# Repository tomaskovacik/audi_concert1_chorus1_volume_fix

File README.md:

> ## ⚠️ v2.0.0 — Important notice
>
> **Firmware v2.0.0 is only suitable for HWv5 boards.** It will NOT work correctly on older hardware revisions (v1–v4).
>
> This release is currently **under real-life / daily-use testing**. If you experience issues, please open a [GitHub issue](https://github.com/tomaskovacik/audi_concert1_chorus1_volume_fix/issues).
>
> ### What changed in v2.0.0 (not in release notes — no PRs were used)
>
> - **Switched to official STMicroelectronics STM32 Arduino core** (replaces Roger Clark's libmaple/stm32duino community core)
> - **Hardware SPI** used for front-panel communication (via STM32 core SPI peripheral)
> - **FlexWire** software I2C library used for TDA7342 volume chip communication on PB10/PB11  
>   (STM32F103C6 has only one I2C peripheral; hardware I2C2 does not exist on this chip)
> - **Persistent config** saved to last flash page (volume level, GALA, TA) — replaces EEPROM emulation from older cores
> - **GALA** (speed-dependent volume) support via VSS pulse timing on PB5
> - **CI** updated to build and release firmware binary automatically on git tags

Software and hardware to fix volume problem on audi concert1/chorus1 units made by blaupunkt. More about this problem in [this](https://github.com/tomaskovacik/audi_concert1_chorus1_volume_fix/wiki/Problem-of-Some-AUDI-Chorus-and-AUDI-Concert-Autoradio-Models,-or-%22Delayed-Action-Mine%22-from-Blaupunkt-Company) wiki page which is copy from [here](https://web.archive.org/web/20071017195907/http://erta.ru/review/chorus-problem_eng.shtml).

#### Compatible radios:

These are 100% compatible, manufactured by Blaupunkt:
```
Audi Chorus - 7 646 243 380 (4B0 035 152)
Audi Chorus A8 - 7 647 243 380
Audi Concert - 7 646 248 380 (4B0 035 186)
Audi Concert A8 - 7 647 248 380 (4D0 035 186A)
Audi Concert Navi - 7 647 249 380 (4B0 035 186B)
AUDI	CONCERT TT AUZ1Z3	7 648 244 380 (4B0 035 186D)
```
Maybe for these, drop me a message with pictures of radio from outside and inside, and I can check if your radio is compatible with this module:
```
AUDI	CHORUS A3	7 640 251 380
AUDI	CHORUS A8	7 648 243 380
AUDI	CHORUS AUZ1Z2	7 647 245 380   4B0 035 152A
AUDI	CHORUS M4 AUZ1Z2	7 648 245 380   4B0 035 152B
AUDI	CHORUS M4 AUZ1Z2	7 648 245 380   4B0 035 152B
AUDI	CONCERT A8	7 648 248 380
AUDI	CONCERT M4 AUZ1Z3	7 648 247 380   4B0 035 186C
```
#### Not compatible radios

Audio Concert made by Panasonic/Matsushita (8L0 035 186A, possible other codes ).This radio from this manufacturer did not have problems with volume (if it has, the problem is in volume rotary encoder)

There are other radios manufactured by Blaupunkt called Audi Concert Plus, which are not compatible:
```
AUDI	CONCERT PLUS AUZ1Z3	7 649 246 380   4B0 035 186E
AUDI	CONCERT PLUS A8 AUZ1Z3	7 649 249 380   4D0 035 186F
```
These use a different design and so are not compatible with this module. I never read that these radios did have a volume problem. If there is one then it is most likely a problem with volume rotary encoder.

#### Issues
Known issues <a href="https://github.com/tomaskovacik/audi_concert1_chorus1_volume_fix/issues">are here</a>

#### Video
Module in action: 

#### Schematics:

Schematics in <a href="https://github.com/tomaskovacik/audi_concert1_chorus1_volume_fix/blob/master/HW/audi_concert1_chorus1_volume_fix/audi_concert1_chorus1_volume_fix.pdf">pdf</a>.

Assemble plan for latest v5 is <a href="https://tomaskovacik.github.io/audi_concert1_chorus1_volume_fix/HW/audi_concert1_chorus1_volume_fix/bom_v5/ibom.html">here</a>. Components with value prefi NP_ are not required (not populated). These are there for future features. 1k_GALA resistor has to be populated if SW with <a href="https://github.com/tomaskovacik/audi_concert1_chorus1_volume_fix/blob/gala/SW/audi_volume_fix_stm32/audi_volume_fix_stm32.ino">gala</a> support is used (SW from gala branch). AP for old v1 hw is <a href="https://raw.githubusercontent.com/tomaskovacik/audi_concert1_chorus1_volume_fix/master/HW/audi_concert1_chorus1_volume_fix/assemble_plan1_0.png">here</a>.

Pictures of finished product:

Bottom side, with PLCC52 socket, inside part of pastic need to be cut:

Upper side, with comments to sockets

How to wire it (currently without intefacing with front pannel)

# COPYING

Everything is under GPLv3

# CONTRIBUTION

Contributions are welcome

# PCBs

PCBs are on sale also as whole product, kitt (PCB, soldered crystals, unsoldered preprogramed IC, pasives,PLCC52 socket)

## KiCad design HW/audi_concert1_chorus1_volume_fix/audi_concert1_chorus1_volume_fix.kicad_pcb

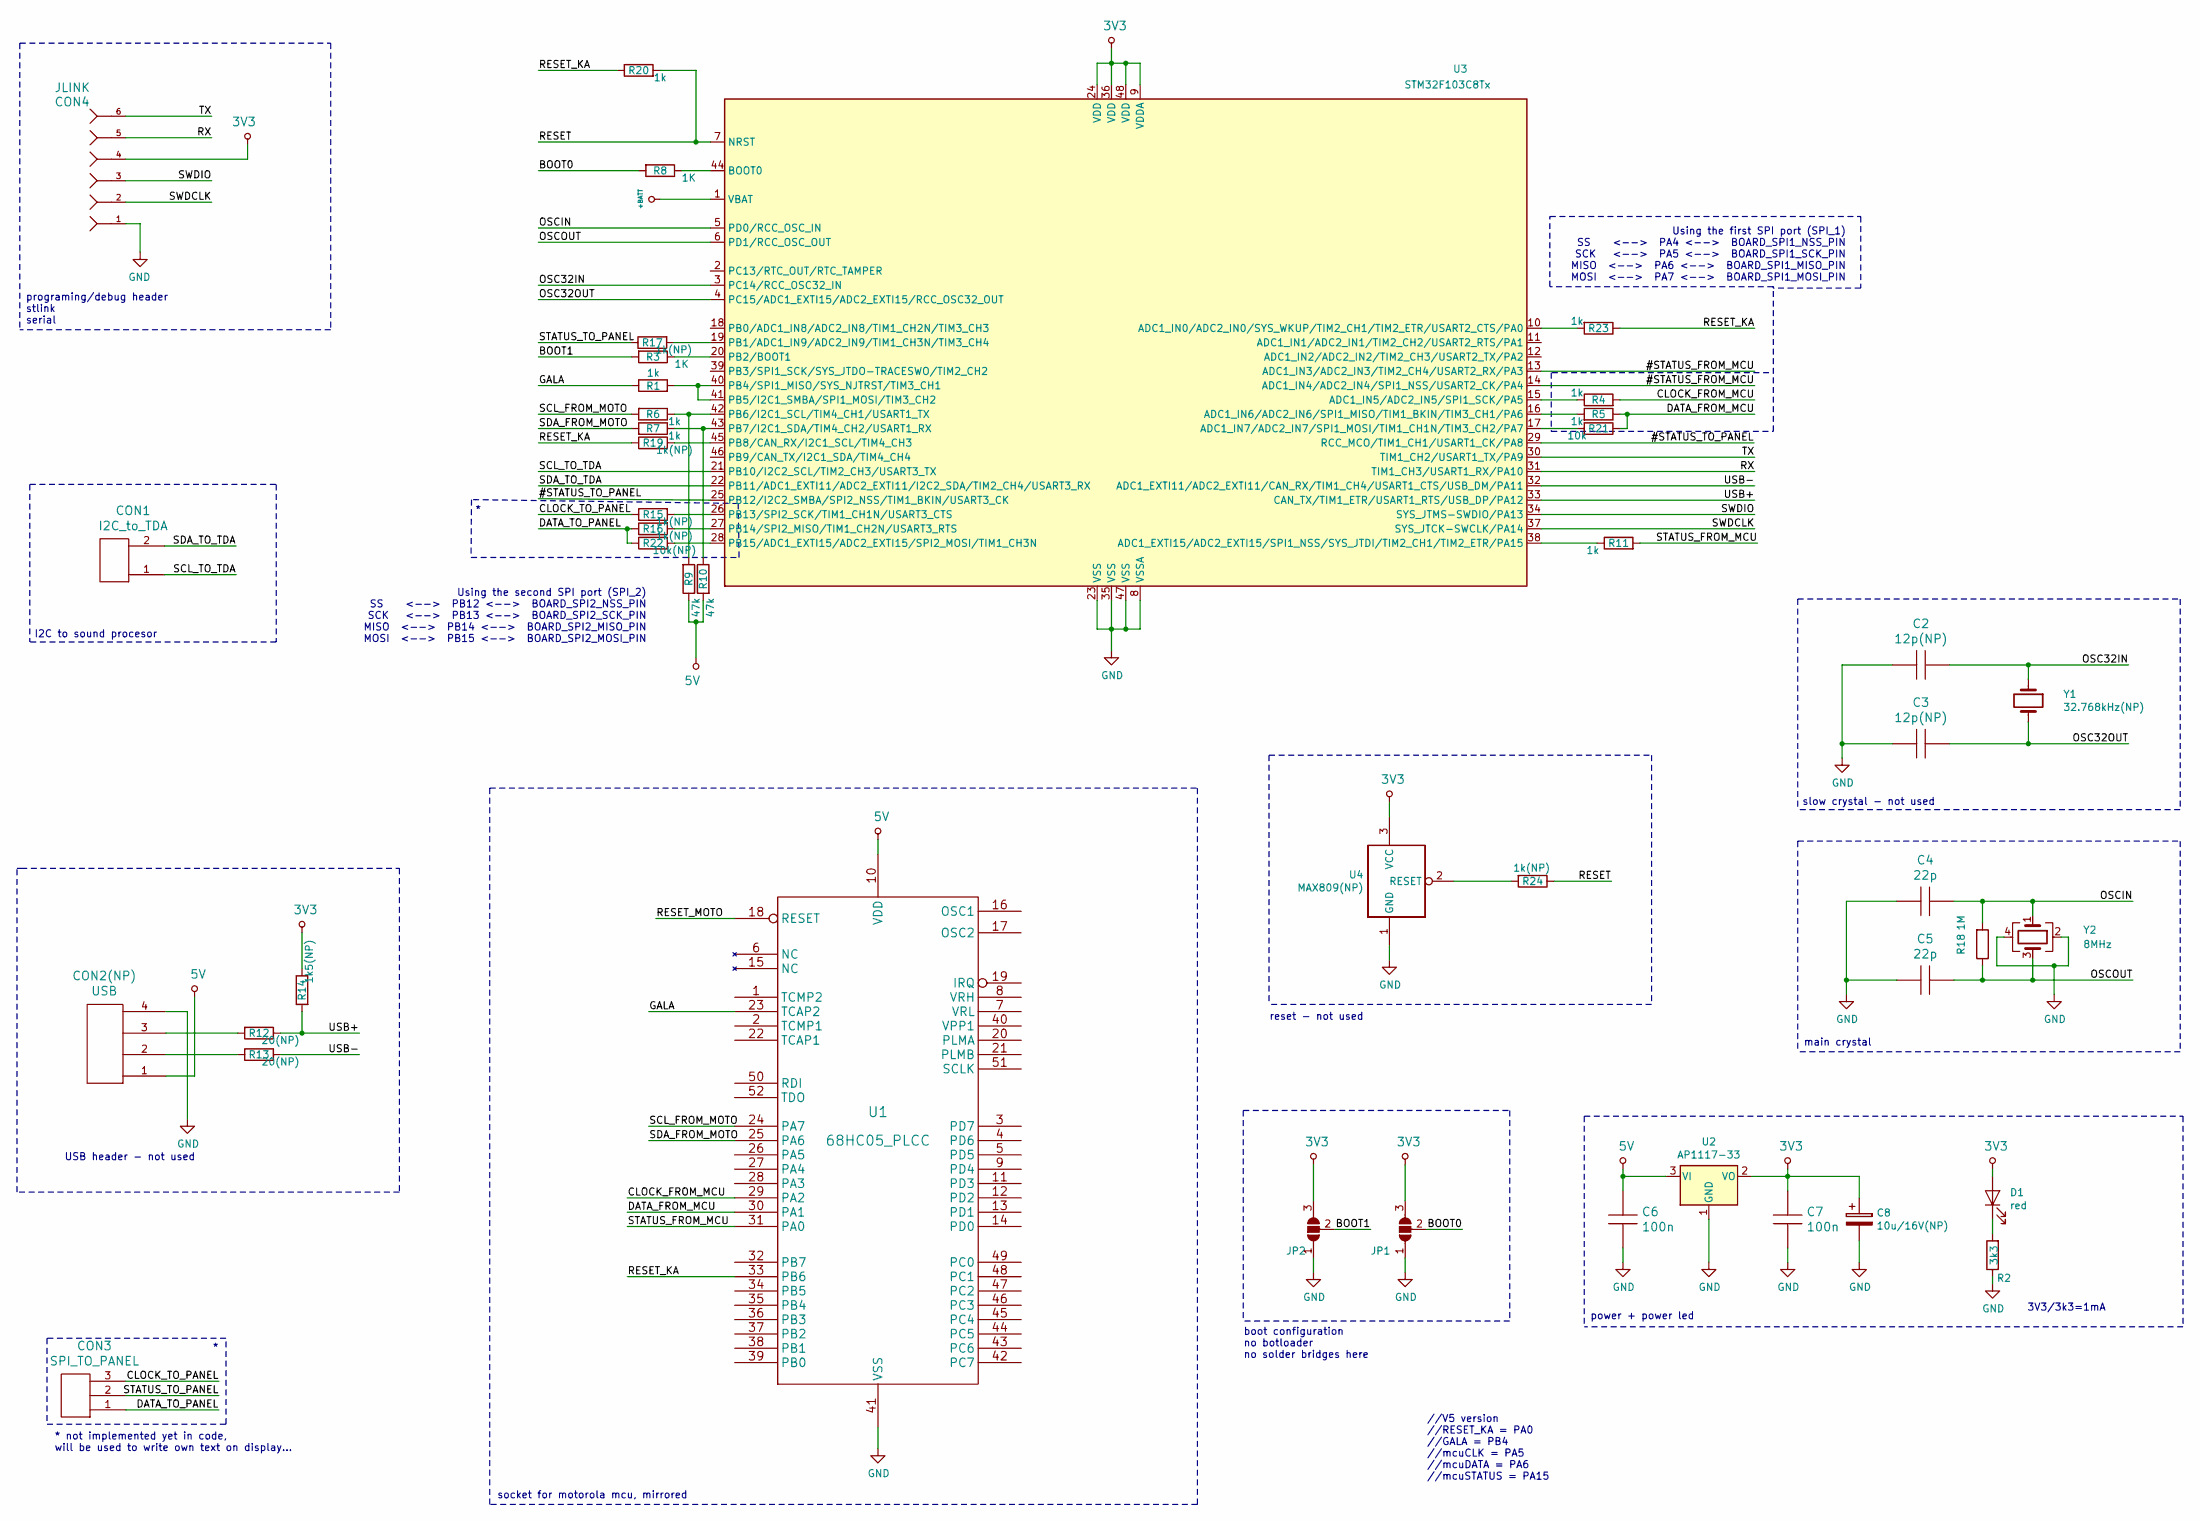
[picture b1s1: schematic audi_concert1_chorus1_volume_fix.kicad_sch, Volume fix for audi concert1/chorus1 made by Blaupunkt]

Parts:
C2, C3: 12p(NP); C_0805_HandSoldering
C4, C5: 22p; C_0805_HandSoldering
C6, C7: 100n; C_0805_HandSoldering
C8: 10u/16V(NP); TantalC_SizeA_EIA-3216_HandSoldering
CON1: I2C_to_TDA; Pin_Header_Straight_1x02
CON2(NP): USB; Pin_Header_Straight_1x04
CON3: SPI_TO_PANEL; Pin_Header_Straight_1x03
CON4: JLINK; Pin_Header_Straight_1x06
D1: red; LED-1206
JP1, JP2: SolderJumper_3_Open; SolderJumper-3_P1.3mm_Open_RoundedPad1.0x1.5mm_NumberLabels
R1, R4, R5, R6, R7, R11, R20, R23: 1k; R_0805_HandSoldering
R2: 3k3; R_0805_HandSoldering
R3, R8: 1K; R_0805_HandSoldering
R9, R10: 47k; R_0805_HandSoldering
R12, R13: 20(NP); R_0805_HandSoldering
R14: 1k5(NP); R_0805_HandSoldering
R15, R16, R17, R19, R24: 1k(NP); R_0805_HandSoldering
R18: 1M; R_0805_HandSoldering
R21: 10k; R_0805_HandSoldering
R22: 10k(NP); R_0805_HandSoldering
U1: 68HC05_PLCC; PLCC-52_mirrored
U2: AP1117-33; AB2_SOT223
U3: STM32F103C8Tx; LQFP-48_7x7mm_Pitch0.5mm
U4: MAX809(NP); SOT-23
Y1: 32.768kHz(NP); Crystal_SMD_3215-2pin_3.2x1.5mm
Y2: 8MHz; Crystal_SMD_5032-4pin_5.0x3.2mm

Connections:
3V3: C7.1, C8.1, CON4.4, D1.2 (A), JP1.3 (B), JP2.3 (B), R14.1, U2.2 (VO), U3.9 (VDDA), U3.24 (VDD), U3.36 (VDD), U3.48 (VDD), U4.3 (VCC)
5V: C6.1, CON2(NP).1, R9.1, R10.2, U1.10 (VDD), U2.3 (VI); also elsewhere on the board
+BATT: U3.1 (VBAT)
/#STATUS_FROM_MCU: U3.13 (ADC1_IN3/ADC2_IN3/TIM2_CH4/USART2_RX/PA3), U3.14 (ADC1_IN4/ADC2_IN4/SPI1_NSS/USART2_CK/PA4)
/#STATUS_TO_PANEL: U3.25 (PB12/I2C2_SMBA/SPI2_NSS/TIM1_BKIN/USART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), U3.29 (RCC_MCO/TIM1_CH1/USART1_CK/PA8)
/BOOT0: JP1.2 (C), R8.2
/BOOT1: JP2.2 (C), R3.2
/CLOCK_FROM_MCU: R4.2, U1.29 (PA2)
/CLOCK_TO_PANEL: CON3.3, R15.1
/DATA_FROM_MCU: R5.1, R21.1, U1.30 (PA1)
/DATA_TO_PANEL: CON3.1, R16.1, R22.1
/GALA: R1.1, U1.23 (TCAP2)
/OSC32IN: C2.1, U3.3 (PC14/RCC_OSC32_IN), Y1.1
/OSC32OUT: C3.2, U3.4 (PC15/ADC1_EXTI15/ADC2_EXTI15/RCC_OSC32_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), Y1.2
/OSCIN: C4.1, R18.2, U3.5 (PD0/RCC_OSC_IN), Y2.1
/OSCOUT: C5.2, R18.1, U3.6 (PD1/RCC_OSC_OUT), Y2.3
/RESET: R20.2, R24.1, U3.7 (NRST)
/RESET_KA: R19.1, R20.1, R23.1, U1.33 (PB6)
/RESET_MOTO: U1.18 (RESET)
/RX: CON4.5, U3.31 (TIM1_CH3/USART1_RX/PA10)
/SCL_FROM_MOTO: R6.2, U1.24 (PA7)
/SCL_TO_TDA: CON1.1, U3.21 (PB10/I2C2_SCL/TIM2_CH3/USART3_TX)
/SDA_FROM_MOTO: R7.2, U1.25 (PA6)
/SDA_TO_TDA: CON1.2, U3.22 (PB11/ADC1_EXTI11/ADC2_EXTI11/I2C2_SDA/T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)
/STATUS_FROM_MCU: R11.2, U1.31 (PA0)
/STATUS_TO_PANEL: CON3.2, R17.1
/SWDCLK: CON4.2, U3.37 (SYS_JTCK-SWCLK/PA14)
/SWDIO: CON4.3, U3.34 (SYS_JTMS-SWDIO/PA13)
/TX: CON4.6, U3.30 (TIM1_CH2/USART1_TX/PA9)
/USB+: R12.1, R14.2, U3.33 (CAN_TX/TIM1_ETR/USART1_RTS/USB_DP/PA12)
/USB-: R13.2, U3.32 (ADC1_EXTI11/ADC2_EXTI11/CAN_RX/TIM1_CH4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)
GND: C2.2, C3.1, C4.2, C5.1, C6.2, C7.2, C8.2, CON2(NP).4, CON4.1, JP1.1 (A), JP2.1 (A), R2.1, U1.41 (VSS), U2.1 (GND), U3.8 (VSSA), U3.23 (VSS), U3.35 (VSS), U3.47 (VSS), U4.1 (GND), Y2.2, Y2.4; also elsewhere on the board
unnamed 32: CON2(NP).2, R13.1; also elsewhere on the board
unnamed 33: CON2(NP).3, R12.2; also elsewhere on the board
unnamed: D1.1 (K), R2.2
unnamed: R1.2, U3.40 (PB4/SPI1_MISO/SYS_NJTRST/TIM3_CH1), U3.41 (PB5/I2C1_SMBA/SPI1_MOSI/TIM3_CH2)
unnamed: R3.1, U3.20 (PB2/BOOT1)
unnamed: R4.1, U3.15 (ADC1_IN5/ADC2_IN5/SPI1_SCK/PA5)
unnamed: R5.2, U3.16 (ADC1_IN6/ADC2_IN6/SPI1_MISO/TIM1_BKIN/T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)
unnamed: R6.1, R9.2, U3.42 (PB6/I2C1_SCL/TIM4_CH1/USART1_TX)
unnamed: R8.1, U3.44 (BOOT0)
unnamed: R7.1, R10.1, U3.43 (PB7/I2C1_SDA/TIM4_CH2/USART1_RX)
unnamed: R11.1, U3.38 (ADC1_EXTI15/ADC2_EXTI15/SPI1_NSS/SYS_JT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)
unnamed: R15.2, U3.26 (PB13/SPI2_SCK/TIM1_CH1N/USART3_CTS)
unnamed: R16.2, U3.27 (PB14/SPI2_MISO/TIM1_CH2N/USART3_RTS)
unnamed: R17.2, U3.19 (PB1/ADC1_IN9/ADC2_IN9/TIM1_CH3N/TIM3_CH4)
unnamed: R19.2, U3.45 (PB8/CAN_RX/I2C1_SCL/TIM4_CH3)
unnamed: R21.2, U3.17 (ADC1_IN7/ADC2_IN7/SPI1_MOSI/TIM1_CH1N/T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)
unnamed: R22.2, U3.28 (PB15/ADC1_EXTI15/ADC2_EXTI15/SPI2_MOSI/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)
unnamed: R23.2, U3.10 (ADC1_IN0/ADC2_IN0/SYS_WKUP/TIM2_CH1/TIM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)
unnamed: R24.2, U4.2 (RESET)

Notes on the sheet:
boot configuration no botloader no solder bridges here
Using the second SPI port (SPI_2) SS <--> PB12 <--> BOARD_SPI2_NSS_PIN SCK <--> PB13 <--> BOARD_SPI2_SCK_PIN MISO <--> PB14 <--> BOARD_SPI2_MISO_PIN MOSI <--> PB15 <--> BOARD_SPI2_MOSI_PIN
power + power led
* not implemented yet in code, will be used to write own text on display...
socket for motorola mcu, mirrored
USB header - not used
Using the first SPI port (SPI_1) SS <--> PA4 <--> BOARD_SPI1_NSS_PIN SCK <--> PA5 <--> BOARD_SPI1_SCK_PIN MISO <--> PA6 <--> BOARD_SPI1_MISO_PIN MOSI <--> PA7 <--> BOARD_SPI1_MOSI_PIN
I2C to sound procesor
3V3/3k3=1mA
slow crystal - not used
//V5 version //RESET_KA = PA0 //GALA = PB4 //mcuCLK = PA5 //mcuDATA = PA6 //mcuSTATUS = PA15
reset - not used
main crystal
programing/debug header stlink serial

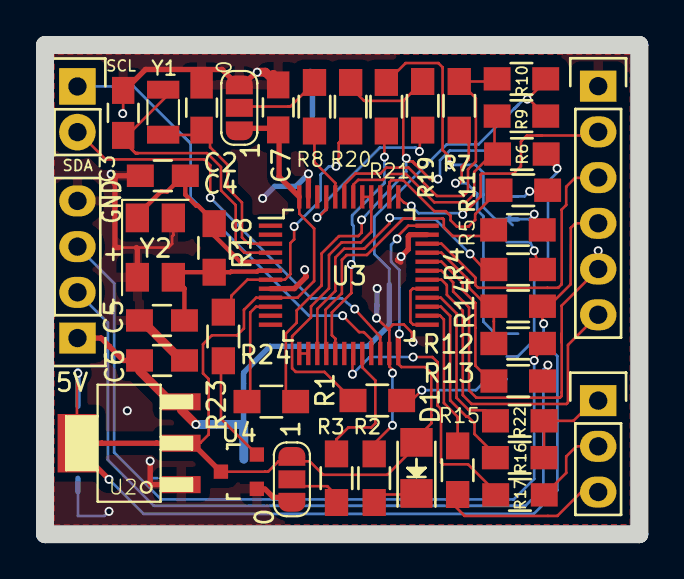
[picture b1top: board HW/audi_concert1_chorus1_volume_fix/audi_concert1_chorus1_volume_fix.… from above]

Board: 2 copper layers, 33.0 x 27.2 mm, 44 parts (1 on the bottom side), 49 nets.

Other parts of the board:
CON2: USB; Pin_Header_Straight_1x04

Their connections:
5V: CON2.1; also elsewhere on the board
GND: CON2.4; also elsewhere on the board
unnamed 32: CON2.2; also elsewhere on the board
unnamed 33: CON2.3; also elsewhere on the board

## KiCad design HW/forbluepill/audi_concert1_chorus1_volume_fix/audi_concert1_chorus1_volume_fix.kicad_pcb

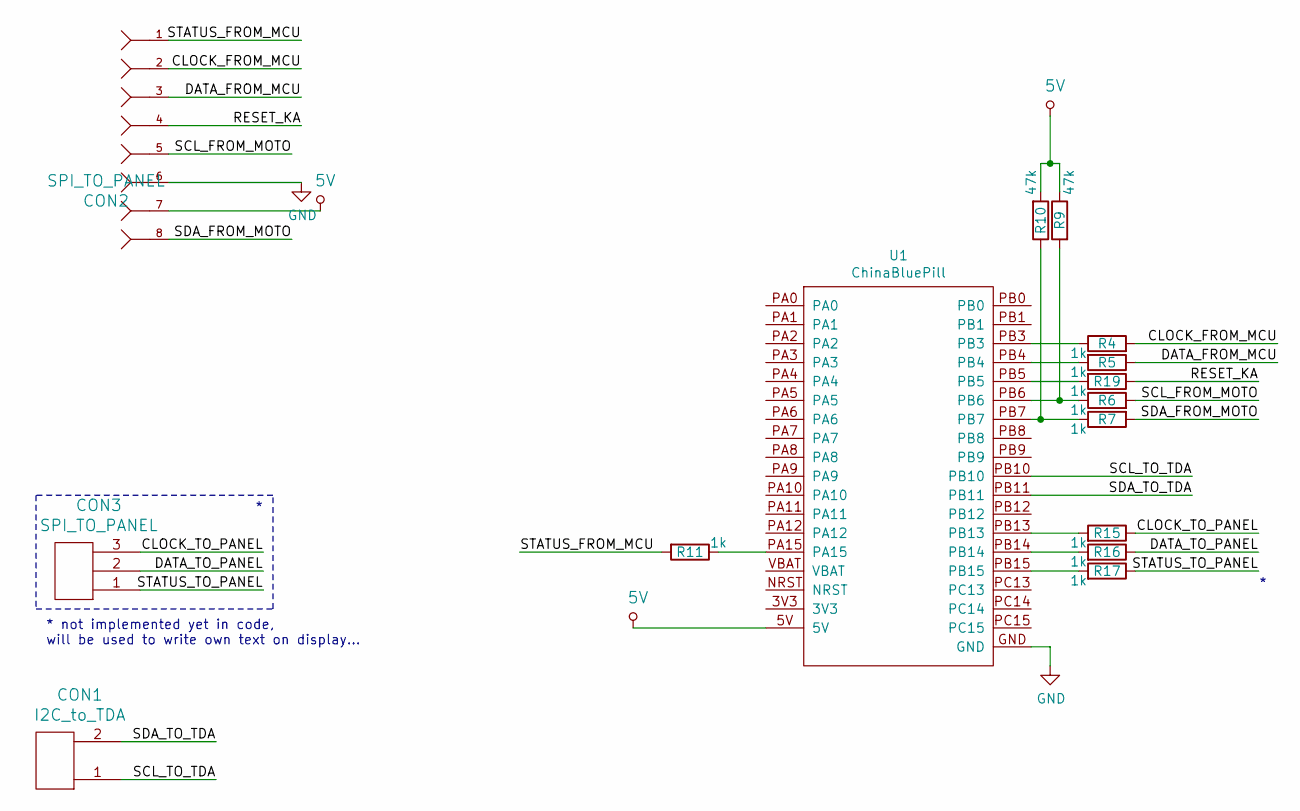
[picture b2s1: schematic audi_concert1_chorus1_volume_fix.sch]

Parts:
CON1: I2C_to_TDA; Pin_Header_Straight_1x02
CON2: SPI_TO_PANEL; Pin_Header_Straight_1x08
CON3: SPI_TO_PANEL; Pin_Header_Straight_1x03
R4, R5, R6, R7, R11, R15, R16, R17, R19: 1k; R_0805_HandSoldering
R9, R10: 47k; R_0805_HandSoldering
U1: ChinaBluePill

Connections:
5V: CON2.7, R9.1, R10.2, U1.5V
/CLOCK_FROM_MCU: CON2.2, R4.2
/CLOCK_TO_PANEL: CON3.3, R15.1
/DATA_FROM_MCU: CON2.3, R5.1
/DATA_TO_PANEL: CON3.2, R16.1
/RESET_KA: CON2.4, R19.1
/SCL_FROM_MOTO: CON2.5, R6.2
/SCL_TO_TDA: CON1.1, U1.PB10
/SDA_FROM_MOTO: CON2.8, R7.2
/SDA_TO_TDA: CON1.2, U1.PB11
/STATUS_FROM_MCU: CON2.1, R11.2
/STATUS_TO_PANEL: CON3.1, R17.1
GND: CON2.6, U1.GND
unnamed: R4.1, U1.PB3
unnamed: R5.2, U1.PB4
unnamed: R6.1, R9.2, U1.PB6
unnamed: R7.1, R10.1, U1.PB7
unnamed: R11.1, U1.PA15
unnamed: R15.2, U1.PB13
unnamed: R16.2, U1.PB14
unnamed: R17.2, U1.PB15
unnamed: R19.2, U1.PB5

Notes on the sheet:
* not implemented yet in code, will be used to write own text on display...

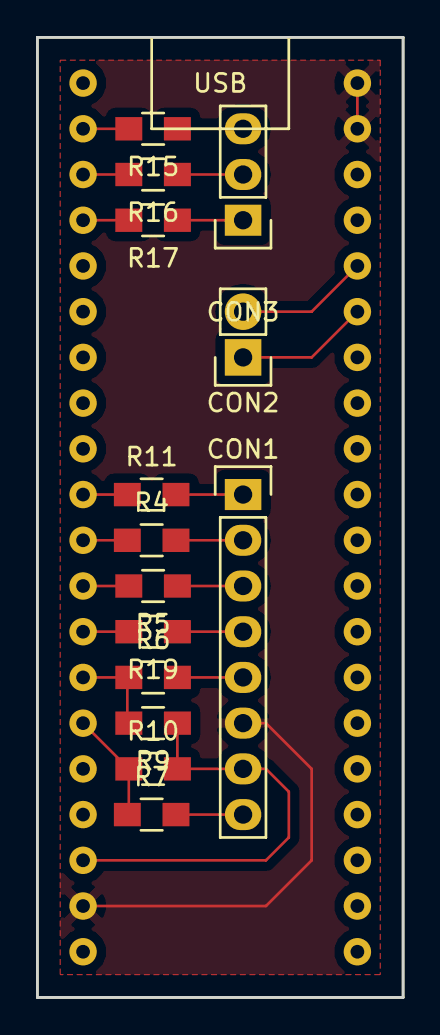
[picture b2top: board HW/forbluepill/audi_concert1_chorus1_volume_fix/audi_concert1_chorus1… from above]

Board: 2 copper layers, 20.3 x 53.3 mm, 15 parts (0 on the bottom side), 22 nets.

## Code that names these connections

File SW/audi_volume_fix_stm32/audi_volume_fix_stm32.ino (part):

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// Define HWV5_BRIDGE to activate bridge mode (active); omit for passive sniff mode.
//
// Bridge pin assignment:
//   MCU side  (SPI1 slave):  PA5=SCK, PA7=MOSI, PA15=STATUS(OUTPUT), PA3=CS
//   Panel side (SPI2 master): PB13=SCK, PB14=MISO, PB15=MOSI, PB1=STATUS(INPUT), PA8=CS
//   GALA: PB5 (TIM3_CH2, speed pulse from HC05 pin23 via 1kΩ — optional)

/* version 5 — bridge mode (replaces passive sniffer with active man-in-the-middle)
mcuCLK    = PA5  (SPI1_SCK  - input, MCU drives CLK)
mcuDATA   = PA7  (SPI1_MOSI - data received by STM32 in slave mode)
mcuSTATUS = PA15 (OUTPUT: STM32 drives STATUS to MCU, acting as front panel)
mcuCS     = PA3  (output: hw-inverted PA15, mirrors SPI1_NSS on board)
panelCLK    = PB13 (SPI2_SCK  output to panel)
panelMOSI   = PB15 (SPI2_MOSI output to panel)
panelMISO   = PB14 (SPI2_MISO input from panel)
panelSTATUS = PB1  (input: panel drives STATUS)
panelCS     = PA8  (output: hw-inverted PB1)
*/
#define HWV5_BRIDGE
#include <SPI.h>
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#include <FlexWire.h>
#include "audi_concert_panel.h"

FlexWire SWire = FlexWire(PB11, PB10);

#ifdef HWV5_BRIDGE
SPIClass SPI_2(PB15, PB14, PB13);  // SPI2: PB13=SCK, PB14=MISO, PB15=MOSI (panel side master)
#endif

#define USE_SERIAL
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

#define DEFAULT_VOL   3
#define DEFAULT_GALA  0   // GALA off by default
#define DEFAULT_TA    3

// GALA speed input pin (PB5 = TIM3_CH2, tied with PB4/TIM3_CH1 — parallel with HC05 pin23, BC558 PNP high-side driver via 1kΩ)
#define GALA_PIN  PB5
/*
    SPI communication between motorola MC68HC05B32 cpu to front panel ST6280
    basics:
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    more data to come.

*/
#define mcuCLK    PA5  // SPI1_SCK  - MCU drives CLK (input, passive sniff)
#define mcuDATA   PA7  // SPI1_MOSI - shared DATA via resistors (input, passive sniff)
#define mcuCS     PA3  // output: mirrors STATUS → HW inverter → SPI1_NSS (PA4)
#define mcuSTATUS PA15
#ifdef HWV5_BRIDGE
// Panel side (SPI2 master) — STM32 acts as Audi MCU toward front panel
#define panelCLK    PB13  // SPI2_SCK  - output to panel
#define panelMOSI   PB15  // SPI2_MOSI - output to panel (10k resistor in HW)
#define panelMISO   PB14  // SPI2_MISO - input from panel (1k resistor in HW)
#define panelSTATUS PB1   // STATUS from panel (input, panel drives this)
#define panelCS     PA8   // CS to panel: output = !PB1 (hw wired to PB12 for inversion)
#endif
#define displayRESET PB8
#define VERSION "2.1-25.05.26-HWv5"

//we are trying to interface with communication to TDA7342 which is 0x44 so...
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void galaRising() {
  TIM2->CNT = 0;
  TIM2->CR1 |= TIM_CR1_CEN;
  attachInterrupt(digitalPinToInterrupt(GALA_PIN), galaFalling, FALLING);
}

void galaFalling() {
  TIM2->CR1 &= ~TIM_CR1_CEN;
  gala_captime = (uint16_t)TIM2->CNT;
  attachInterrupt(digitalPinToInterrupt(GALA_PIN), galaRising, RISING);
}

void setup ()
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
  // Enable SPI1 and AFIO clocks
  RCC->APB2ENR |= RCC_APB2ENR_AFIOEN | RCC_APB2ENR_SPI1EN;
  // Disable JTAG, keep SWD (SWJ_CFG=010) → frees PB3/PB4/PA15 for GPIO; clear SPI1_REMAP → default pins
  AFIO->MAPR = (AFIO->MAPR & ~(AFIO_MAPR_SWJ_CFG | AFIO_MAPR_SPI1_REMAP)) | AFIO_MAPR_SWJ_CFG_JTAGDISABLE;

#ifdef HWV5_BRIDGE
  // ── Bridge mode: STM32 acts AS front panel to radio MCU ──────────────────────────
  // STM32 drives STATUS (PA15) as output; watches CLK (PA5) for byte framing.
  // SPI1 slave with software NSS + RXNE interrupt for byte capture.
  pinMode(mcuCLK, INPUT_PULLUP);   // PA5: SCK from MCU (input)
  attachInterrupt(digitalPinToInterrupt(mcuCLK), mcuClkChange, CHANGE);
  pinMode(mcuDATA, INPUT_PULLUP);  // PA7: MOSI from MCU (input)
  pinMode(mcuSTATUS, OUTPUT);      // PA15: STM32 drives STATUS to MCU (output)
  digitalWrite(mcuSTATUS, HIGH);   // idle HIGH
  pinMode(mcuCS, OUTPUT);          // PA3: hardware-inverted STATUS → PA4/NSS
  digitalWrite(mcuCS, LOW);        // STATUS HIGH → CS LOW
  // SPI1 slave: call SPI.begin() to configure AF pins, then patch to slave mode
  SPI.begin();
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  NVIC_EnableIRQ(SPI1_IRQn);

  // ── Bridge mode: STM32 acts AS radio MCU to front panel ──────────────────────────
  // Panel drives STATUS; STM32 drives CLK (PB13) between packets as GPIO HIGH.
  // SPI2 is only activated inside sendToPanel()/receivePanelPacket().
  pinMode(panelCLK, OUTPUT);
  digitalWrite(panelCLK, HIGH);      // CLK idle HIGH = no transfer in progress
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  digitalWrite(panelCS, LOW);        // STATUS idle HIGH → CS LOW
#else
  // ── Sniff mode: passive monitoring of MCU↔panel SPI bus ─────────────────────────
  // STATUS ISR gates NSS (PA3→PA4/NSS) to frame each byte.
  pinMode(mcuSTATUS, INPUT_PULLUP);
  pinMode(mcuCS, OUTPUT);
  digitalWrite(mcuCS, !digitalRead(mcuSTATUS));
  attachInterrupt(digitalPinToInterrupt(mcuSTATUS), mcuStatusChange, CHANGE);

  // PA4/NSS, PA5/SCK, PA7/MOSI must be INPUT before enabling SPI1
  pinMode(PA4, INPUT);  // NSS driven via PA3→inverter
  pinMode(PA5, INPUT);
  pinMode(PA7, INPUT);

  // SPI1 slave: SSM=0 → hardware NSS (PA4).  NSS LOW = selected = shift reg active.
  SPI1->CR1 = 0;  // MSTR=0, SSM=0, CPOL=0, CPHA=0
  SPI1->CR1 |= SPI_CR1_SPE;
  SPI1->CR2 = 0;  // no interrupts; loop() polls SR
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
  // GALA: TIM2 at 1µs resolution for speed pulse measurement
  if (cfg.gala > 0) {
    pinMode(GALA_PIN, INPUT_PULLDOWN);
    RCC->APB1ENR |= RCC_APB1ENR_TIM2EN;
    TIM2->PSC = 71;       // 72MHz / (71+1) = 1MHz = 1µs ticks
    TIM2->ARR = 0xFFFF;
    TIM2->CNT = 0;
    TIM2->CR1 = 0;        // stopped
    TIM2->EGR = TIM_EGR_UG;  // force update to load PSC/ARR
    attachInterrupt(digitalPinToInterrupt(GALA_PIN), galaRising, RISING);
  }

#ifdef USE_SERIAL
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    // "GALA OFF" or "GALA X  " — GALA level 0-5
    if (_data[2]=='G' && _data[3]=='A' && _data[4]=='L' && _data[5]=='A' && _data[6]==' ') {
      if (_data[7]=='O' && _data[8]=='F' && _data[9]=='F') {
        cfg.gala = 0;
#ifdef USE_SERIAL
        USEDSERIAL.println(F("CFG_PANEL: gala=0 (OFF)"));
#endif
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{
    if (digitalRead(mcuSTATUS)) {
        // STATUS RISING → deselect SPI1 (byte complete)
        digitalWrite(mcuCS, LOW);   // PA3 LOW → inverter → NSS HIGH

        // Harvest the completed byte immediately — before loop() gets a chance to run
        if (SPI1->SR & SPI_SR_RXNE) {
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        // else: CLK LOW = more bytes coming, busy stays 1
    } else {
        // STATUS FALLING → select SPI1 (new byte starting)
        digitalWrite(mcuCS, HIGH);  // PA3 HIGH → inverter → NSS LOW
        panel_message.busy = 1;
    }
}
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
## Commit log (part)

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2018-09-21 HW part
2018-09-21 png with white BG colour
2018-09-21 sw part
2018-09-24 separete functions for un/mute volume down/up, autoset loudness based on volume, config mode on serial debug
2018-09-25 pictures, of working proto, with USB fix
2018-09-25 readme update
2018-09-26 separe function for loudness setting
2018-10-25 formating in readme
2018-10-26 new pics
2018-10-26 how to connect on picture
2018-12-29 gerber filesgerbers/
2018-12-29 delete
2018-12-29 readme
2019-01-02 v2.0 files
2019-01-02 assemble plan form v1.0
2019-01-02 assemble plan info in readme
2019-01-04 small changes probably not important ...
2019-01-06 kicad files update
2019-01-06 update pictures
2019-01-06 fix assemble plan for 1.0boards
2019-01-20 url to store at tindie
2019-03-12 fix loudness /o\
2019-03-16 formating
2019-03-16 should be 0x10 not 10
2019-03-16 do not reset saved_volume to start_volume value
2019-03-16 try fix #3
    logic: send mute data only if volume is 0xFF
2019-03-22 using header file for panel codes
2019-03-22 fix #6
2019-03-22 fix typoe FADE
2019-03-22 Revert "try fix #3"
    This reverts commit 25e89c3670227bfe58622b0d499b7f2911ed3e48.
2019-03-22 remove unsuded TA_volume variable
2019-03-22 fix #3
2019-03-22 readme update about tindie store
2019-03-24 remove unused hw
2019-03-24 move hw files
2019-03-24 remove
2019-03-24 move files
2019-03-24 Revert "move files"
    This reverts commit 8483dbe1d694c7ac6184a05f3c0c4e1058d471e7.
2019-03-24 Revert "remove"
    This reverts commit 13896726668c11aed2890708720dc57b9e7a53ad.
2019-03-26 debug variable, fix #4, formating, version on serial
2019-03-26 multiple changes, volume mode configure over serial (use v key), debug(d) and debug2 (D) switched over serial, try to find simple algoritm for mute packet, instead of marking every posible scenario w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
2019-03-26 in if use == not =git diff . moron!
2019-03-26 utime change grab_volume to 1 then set it to 0 where it's needed
2019-03-26 config volume mode over panel
2019-03-26 HW part for GALA support
2019-03-27 revert
2019-03-27 panel text TELEFON support
2019-03-27 mute is now send based on events on panel bus or i2c bus ...
2019-03-27 gala support in HW
2019-03-27 missin break in switch
2019-03-27 try to fix mute from main MCU
2019-03-27 cleanup
2019-03-29 update readme, nostandalone folder in HW!
2019-03-29 start conditions are muted/volume=0xff
2019-03-29 TAPE load/eject mutting works
2019-03-29 formating, fix input=RADIO marking, restore volume if TP-INFO is showed on display, probably need more tests
2019-04-02 hw, silkscreen positions
2019-04-04 version output on serial
2019-04-04 grab_volume is always 1 before switch
2019-04-06 fix missing grab_volume=0
2019-04-08 Update audi_volume_fix_stm32.ino
    SerialDebug enabling char uppercase just like Version?
2019-04-08 wdp = rdp = dwdp = drdp = 0;
2019-04-15 branch identification
2019-04-15 string devel in version variable
2019-04-16 formating, option for just dumping I2C data
2019-07-18 assemble_plan
2019-10-16 pcb update
2019-10-16 fix #14
2019-10-16 cleanup comment after #14
2019-10-16 fix #14, support for remtoe controle
2019-10-18 version info update
2019-11-13 debug display data: panel start and BOSE
2019-11-13 DIAG. on panel
2019-11-29 link to video
2019-12-15 assamble plan
2019-12-15 lines to represent wires required to bypas I2C lines
2019-12-30 serial info rewrite
2020-01-03 cacheudate
2020-01-07 udpate
2020-01-08 custom volume loudness map init
2020-01-08 Revert "custom volume loudness map init"
    This reverts commit 32f97d021bc654989fd139f5b107d7119f33c96e.
2020-03-13 v2.0
2020-03-14 galabranchINIT
2020-03-14 fixmasterbranchNOTE
2020-03-16 read spead from GALA pin
2020-03-21 astm32core start move to it
2020-03-21 stupid stm32_core fucked my bluepil piss on them, amaters
2020-03-30 eeprom start
2020-03-30 investigating config menu (pressed TP while starting radio
2020-04-02 new kicad version ?
2020-04-02 corect #define placemenet
2020-04-08 gala update
2020-04-09 save to eeprom config VOL/GALA/TA
2020-04-09 split setloudness function to set/send_loudness functions for GALA purpose
2020-04-09 setting volume/loudness based on volume
2020-04-09 start volume read from config menu
2020-04-10 seting volume based on speed
2020-04-10 break in swith
2020-04-10 debug info
2020-04-10 Revert "debug info"
    This reverts commit b93d9c2387f8b277e1fb246047309ef7ee348311.
2020-04-10 Revert "break in swith"
    This reverts commit 444a5d6e7071174c725051a6c0eb62404441af78.
2020-04-11 hw v2
2020-04-11 HW v3
2020-04-11 fix comment position
2020-04-11 audi_concert1_chorus1_volume_fix_v1.pro
2020-04-11 v1 hw
2020-04-11 misc files
2020-04-11 gala pin for v1
2020-04-11 cleanup in HW files
2020-04-11 again recreate devel branch from master
2020-04-11 small fixies from original devel code
2020-04-12 silk screen positioning
2020-04-12 calculation char to dec
2020-04-25 branchname
2020-04-25 config stored in eeprom
2020-04-25 start volume is set based on eeprom settings
2020-04-25 gala info
2020-04-26 set_volume()->send_volume(), split send_loudness to set_loudness and send_loudnes
2020-04-26 volume is always fixed, dumping data is configurable over serial, by presing D or d
2020-04-26 move repeated code in send_volume()
2020-04-26 always fix volume
2020-04-26 remove unuset _gala variable
2020-04-30 disable volume or loudness IGNORING message
2020-05-14 hw v3 - buggy
2020-05-14 hw v4
2020-05-15 change pin defines displayX -> mcuX
2020-05-15 change pin define for RESET back to displayRESET, it is not split because line has no resistor inline between mcu and display
2020-09-16 assemble plan in pdf for v4
2020-09-16 bom for v4
2020-09-16 schematics, pcb and assemble plan for v4 in case of v1 code is used
2020-09-16 ibom for v1 boards
2020-09-16 support from v4 boards in v1 sw
2020-09-16 minor changes
2020-09-16 v4 schematics
2020-09-16 new v4 schematics in png
2020-09-16 fixies in eeprom writing and calculating crc
2020-09-16 bump hw version to 4.0audi_concert1_chorus1_volume_fix.kicad_sch
2020-09-16 bump version in schematics to 4.0
2020-11-20 HW v3 SW mod
2020-11-20 avarange speed on 1000 samples
2020-11-20 uint cannot be negative
2020-11-20 add some default return values
2020-11-20 avarange speed on 1000 samples, null captime after calculations
2020-12-16 notes
2020-12-16 fix resistors are 0805
2020-12-17 fix for v3 HW
2020-12-17 calculate speed based on 1000 measures of pulse
2020-12-17 galabranch in version info in serial print
2020-12-17 displayRESETstate based on pin value at boottime
2020-12-17 comment out msg about ignoring volume and loudness command
2020-12-17 comment out switch dump and fix option over serial
2020-12-17 remove wdp = rdp = dwdp = drdp = 0 when reset line low
2020-12-17 msg on serial when gala kick in
2020-12-17 mute audio prior to set volume to zero, to avoid small noice when switching off on BOSE
2020-12-17 removed 5ms delay after mutting packet
2020-12-17 current volume when off is 0xFF = zero, this make volume goes nicely from silent to preset value at boot
2021-01-20 hw versin in verbose output
2021-04-08 removed outdated HW version 1.0 bom
2021-07-17 hw changes
2021-09-06 vias changed to 0.5/0.3
2021-09-06 gala input fix 11+10 togeter
2021-09-07 change calculating averaging on 10 meassures
2021-10-17 changes to loudnes handling in gala routine in main loop (from ++ to --)
2021-10-17 serial output is enabled based on define USE_SERIAL
2021-10-17 24mA, halt the previous consuption in offmode
2021-10-17 1ms delay also works ...
2021-10-17 1.0-17.10.21 - disable dumping data, 24mA consuption, with simple yield() hack
2021-10-17 bin with 966b8d4
2021-10-17 current bins
2021-10-17 move bins to folder bins
2021-10-17 add prev. bins
2021-10-17 shell script to upload generic bootloader using stlinkv2
2021-10-19 upload script
2021-10-24 buggy version
2021-10-25 fix of fix, forgot that i am callig delay() on more then one place, which was sleeping mcu in not good places
2021-10-25 new stm32duino core version
2021-10-25 new version
2021-10-25 fastboot bootloader binary and shell script for uploading it
2021-11-10 combined bot+firmware binaries
2021-11-11 new file names for firmwares
2021-11-12 confgurng which Serial port use
2021-11-12 remove nasty lowpowermode
2021-11-12 comments about serials
2021-11-12 comments about enableDebugPorts for no usb upload
2021-11-12 comment about enableDebugPorts
2021-11-14 #ifdef USE_SERIAL
2021-11-14 HW v5
2021-11-14 HWv5 fix
2022-01-22 kicad6
2022-02-02 better start volume
2022-02-02 current_bin_for_v4
2022-02-24 move old firmware to old dir
2022-02-24 lower start volume
2022-02-25 lower volume
2022-02-25 serial upload for linux
2022-03-30 USE_SERAL -> USE_SERIAL
2022-03-30 update date version
2022-05-09 bom for purple v5audi_concert1_chorus1_volume_fix/bom_v5/
2022-05-09 new files version
2022-05-09 v5 firmware
2022-05-09 fix previous commit
2022-05-09 new version kicad
2022-11-18 bin for WHv5
2022-11-18 hwv5
2023-02-15 Update audi_volume_fix_stm32.ino
    mcuSTATUS for HWV3 branch (tested on HWV1 board) and USE_SERIAL typo.
    Optionally version changed for easier date reading. This can be ignored.
2023-03-11 typo
2023-03-13 clear talk about #define vers. HW version in comment
2026-02-07 bin for HW5 with serial1(HW) enabled
2026-05-10 fix: buffer overflows, ring-buffer overruns, VERSION string, comment bug, printInfo guard; fix README typos
    Agent-Logs-Url: https://github.com/tomaskovacik/audi_concert1_chorus1_volume_fix/sessions/fa6504bc-be04-4f02-bc67-4147aaaf95b1
2026-05-10 docs: update BOM link to v5 and correct version reference in README
    Agent-Logs-Url: https://github.com/tomaskovacik/audi_concert1_chorus1_volume_fix/sessions/d393f54c-02be-4289-b032-f59a7fdd8699
2026-05-10 Replace set_volume_up/down if-else ladders with PROGMEM volume_steps array
    Agent-Logs-Url: https://github.com/tomaskovacik/audi_concert1_chorus1_volume_fix/sessions/a9f7ffe0-c0cc-40a7-bf9e-222aba67dba9
2026-05-10 Cache pgm_read_byte result in local variable to avoid double flash reads
    Agent-Logs-Url: https://github.com/tomaskovacik/audi_concert1_chorus1_volume_fix/sessions/a9f7ffe0-c0cc-40a7-bf9e-222aba67dba9
2026-05-10 Fix mute/unmute saved_volume sync and remove mute=1 hack in set_volume_up/down
    Agent-Logs-Url: https://github.com/tomaskovacik/audi_concert1_chorus1_volume_fix/sessions/a73278d9-17d2-45fb-8737-e8d7c8a18151
2026-05-10 Add branches_compare.md with devel/master/gala branch comparison
2026-05-10 Fix branches_compare.md with correct devel vs master comparison
2026-05-10 Add GitHub Actions workflow for compiling sketches
2026-05-10 Switch from SlowSoftWire to FlexWire in compile workflow
2026-05-10 Replace SlowSoftWire with FlexWire for I2C
2026-05-10 Remove EEPROM from libraries - it is bundled with STM32 core
2026-05-10 Add Wire_slave library to compile workflow
2026-05-12 convert _msg[] and data[] from 2D arrays to 1D circular arrays
    Agent-Logs-Url: https://github.com/tomaskovacik/audi_concert1_chorus1_volume_fix/sessions/e8062f6b-d08f-4a90-a7be-9941cd270a32
2026-05-12 add PACKET_IDX macro to encapsulate circular array index calculation
    Agent-Logs-Url: https://github.com/tomaskovacik/audi_concert1_chorus1_volume_fix/sessions/e8062f6b-d08f-4a90-a7be-9941cd270a32
2026-05-12 add CircularPacketBuffer struct with read/write/commit/available; replace raw arrays with panel_message and i2c_data objects
    Agent-Logs-Url: https://github.com/tomaskovacik/audi_concert1_chorus1_volume_fix/sessions/af5f186a-f925-4d40-ab33-d41c73154ec0
2026-05-12 address review feedback: busy→bool, split write() post-increment, fix typo
    Agent-Logs-Url: https://github.com/tomaskovacik/audi_concert1_chorus1_volume_fix/sessions/af5f186a-f925-4d40-ab33-d41c73154ec0
2026-05-14 Remove Wire_slave library from compile.yml
    Removed 'Wire_slave' library from the workflow configuration, it is part of stm32duino
2026-05-16 ci: move build workflow to legacy stm32duino
2026-05-16 deleted old hw bin
2026-05-16 no bootloader = not ttyACM port
2026-05-16 Initial plan
2026-05-16 fix: use dedicated volume recalc flag to suppress spurious mute
    Agent-Logs-Url: https://github.com/tomaskovacik/audi_concert1_chorus1_volume_fix/sessions/8522ce3f-b7ca-4807-b6a5-26b2c527c888
2026-05-16 HW update
2026-05-16 fix typos
